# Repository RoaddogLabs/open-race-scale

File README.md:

# open-race-scale
# 
This is the Roaddog Labs fork of Open Race Scale, the open hardware
race car scale from Andrew Jenkins at
https://github.com/jenkinsracing/open-race-scale used under OSHWA and
LGPL 3.0 license.  [Original README.md](orig_README.md)

This fork deals with hardware implementation, hardware packaging and
PCB/PCBA design and fabrication.  This fork uses the software/firmware
from the upstream fork.  Please issue software/firmware pull requests to
the upstream repo.  Pull requests for hardware implementation in this
fork are more than welcome.

The `electrical` dir contains circuit designs and PCB/PCBA info.  It
includes the reference design from the upstream master that uses Chengbo HX711 carriers, a Pi Zero W
based control board with integrated HX711 load cell amps (no carriers) and Pi Hat design using Sparkfun HX711 formfactor carriers.

The `mechanical` dir contains a reference scale pad design and enclosure designs for the various controller boards.

Original designs from Roaddog Labs Ltd are released per the Open Source
Hardware Association guidelines for open source hardware at
http://www.oshwa.org/definition/.

Material specific to the components and documentation that is not
derived from other sources are released under the Creative Commons
Attribution 4.0 International license.

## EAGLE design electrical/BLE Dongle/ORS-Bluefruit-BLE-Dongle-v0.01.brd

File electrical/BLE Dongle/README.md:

# open-race-scale
# 

This is a Bluetooth LE dongle that transmits data from the scale pad to the mobile device.

There is no software or firmware at this time.  This is a reference design using an Adafruit Bluefruit nRF52 module and a Chenbo HX711 module.

This is the Roaddog Labs fork of Open Race Scale, the open hardware
race car scale from Andrew Jenkins at
https://github.com/jenkinsracing/open-race-scale used under OSHWA and
LGPL 3.0 license.  

Original designs from Roaddog Labs Ltd are released per the Open Source
Hardware Association guidelines for open source hardware at
http://www.oshwa.org/definition/.

Material specific to the components and documentation that is not
derived from other sources are released under the Creative Commons
Attribution 4.0 International license.

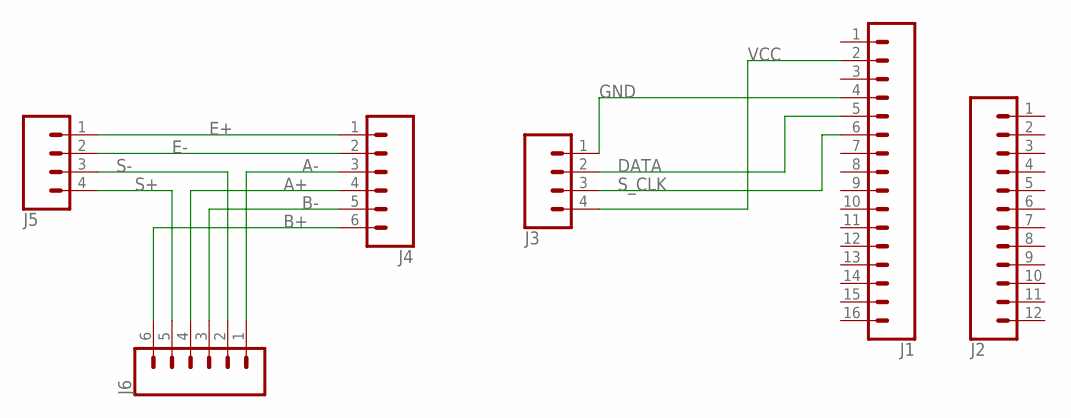
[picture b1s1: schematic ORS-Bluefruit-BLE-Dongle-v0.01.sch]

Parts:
J1: CONN_16; 1X16
J2: CONN_12; 1X12
J3: CONN_04; 1X04
J4, J6: CONN_06SILK_FEMALE_PTH; 1X06
J5: CONN_04SCREW; SCREWTERMINAL-3.5MM-4

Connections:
A+: J4.4, J6.4
A-: J4.3, J6.1
B+: J4.6, J6.6
B-: J4.5, J6.3
DATA: J1.5, J3.2
E+: J4.1, J5.1
E-: J4.2, J5.2
GND: J1.4, J3.1
S+: J5.4, J6.5
S-: J5.3, J6.2
S_CLK: J1.6, J3.3
VCC: J1.2, J3.4

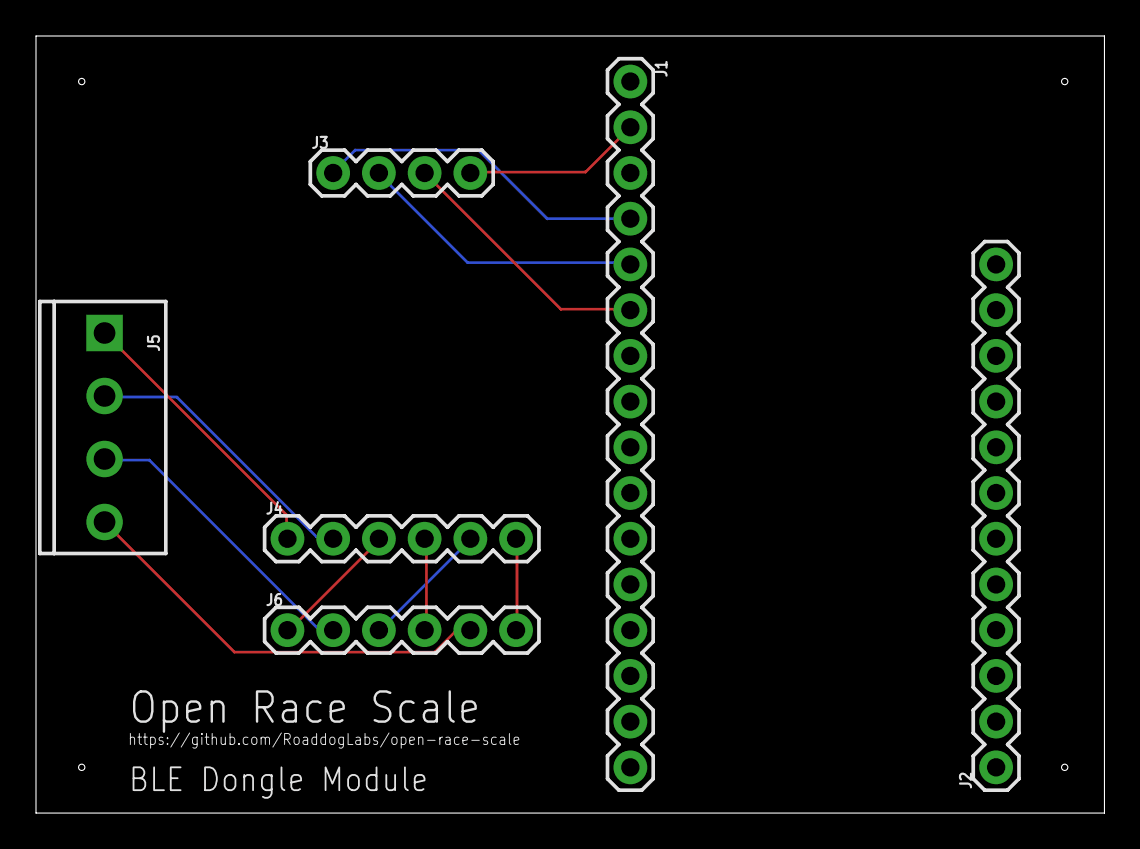
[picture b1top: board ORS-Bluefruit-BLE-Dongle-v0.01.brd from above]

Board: 2 copper layers, 59.4 x 43.2 mm, 6 parts (0 on the bottom side), 12 nets.

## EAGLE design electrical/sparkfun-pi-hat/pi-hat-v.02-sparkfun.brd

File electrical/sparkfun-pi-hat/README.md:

### Open Race Scale Sparkfun HX711 carrier board control board

***THIS BOARD IS NOT YET VALIDATED***

This is an early release version of the control board using Sparkfun HX711 carriers ( https://www.sparkfun.com/products/13879?_ga=2.157347578.176752245.1497484451-1883676811.1497484451 ).  It is not yet ready for production.  It has passed Eagle ERC and DRC for Seeed Fusion PCB.

Forked from https://github.com/jenkinsracing/open-race-scale by Andrew Jenkins license OSHW/public domain, software LGPL 2.0.

Original designs from Roaddog Labs Ltd are released per the Open Source
Hardware Association guidelines for open source hardware at
http://www.oshwa.org/definition/.

Material specific to the components and documentation that is not
derived from other sources are released under the Creative Commons
Attribution 4.0 International license.

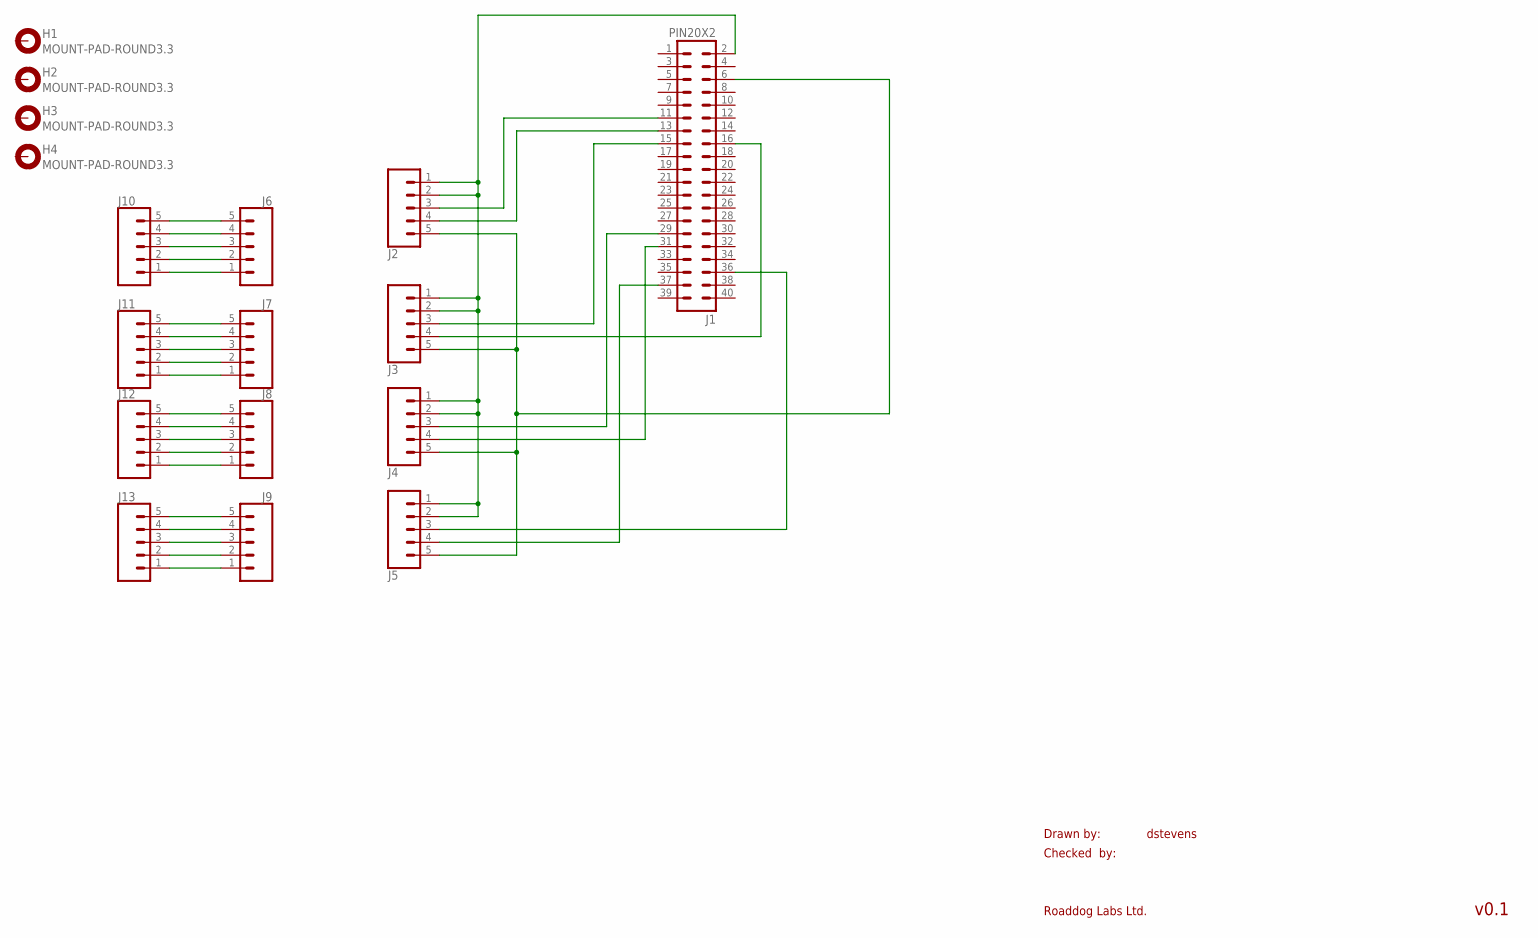
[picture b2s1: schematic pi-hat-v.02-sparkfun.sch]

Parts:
H1, H2, H3, H4: MOUNT-PAD-ROUND3.3; 3,3-PAD
J1: PIN20X2; PIN_20X2
J2, J3, J4, J5, J6, J7, J8, J9, J10, J11, J12, J13: CONN_05; 1X05

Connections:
unnamed: J6.5, J10.5
unnamed: J6.4, J10.4
unnamed: J6.3, J10.3
unnamed: J6.2, J10.2
unnamed: J6.1, J10.1
unnamed: J7.5, J11.5
unnamed: J7.4, J11.4
unnamed: J7.3, J11.3
unnamed: J7.2, J11.2
unnamed: J7.1, J11.1
unnamed: J8.5, J12.5
unnamed: J8.4, J12.4
unnamed: J8.3, J12.3
unnamed: J8.2, J12.2
unnamed: J8.1, J12.1
unnamed: J9.5, J13.5
unnamed: J1.2, J2.1, J2.2, J3.1, J3.2, J4.1, J4.2, J5.1, J5.2
unnamed: J1.6, J2.5, J3.5, J4.5, J5.5
unnamed: J1.11, J2.3
unnamed: J1.13, J2.4
unnamed: J1.15, J3.3
unnamed: J1.16, J3.4
unnamed: J1.37, J5.4
unnamed: J1.36, J5.3
unnamed: J1.31, J4.4
unnamed: J1.29, J4.3
unnamed: J9.4, J13.4
unnamed: J9.3, J13.3
unnamed: J9.2, J13.2
unnamed: J9.1, J13.1

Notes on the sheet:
Drawn by:
Checked by:
Roaddog Labs Ltd.
dstevens
v0.1

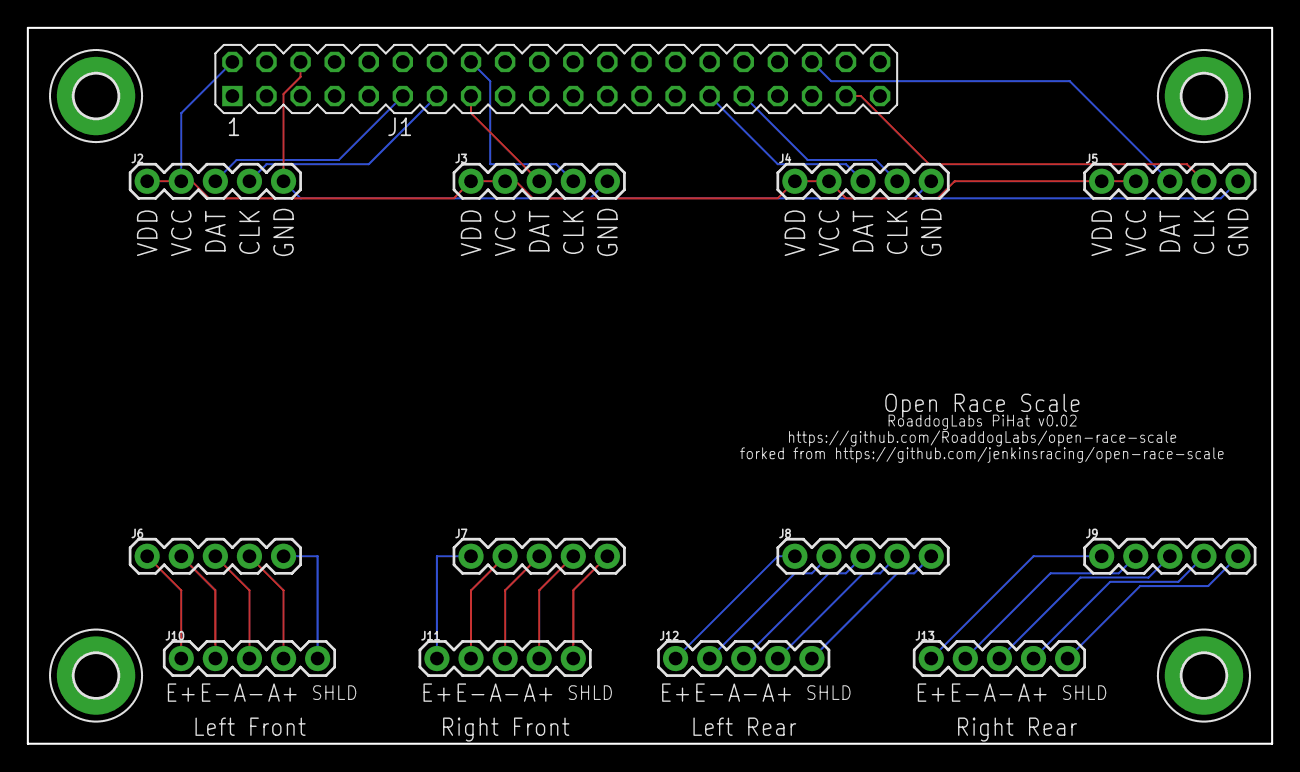
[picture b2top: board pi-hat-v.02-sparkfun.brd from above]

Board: 2 copper layers, 92.7 x 53.3 mm, 17 parts (0 on the bottom side), 30 nets.

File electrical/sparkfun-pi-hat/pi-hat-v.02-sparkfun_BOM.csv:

Designator,Pololu SKU,Qty,
J1,1037,1,https://www.pololu.com/product/1037
"J2,J3,J4,J5,J6,J7,J8,J9",1015,8,https://www.pololu.com/product/1015
"J10,J11,J12,J13",965,1,https://www.pololu.com/product/965

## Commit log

2017-06-26 add schematic and board files for sparkfun pihats
2017-06-26 update schematic and board, generate gerbers
2017-06-27 plate through holes, upload BOM
2017-06-27 update gerbers
2017-07-01 bom for first batch of prototypes
2017-07-10 update readme for pi deployement
2017-07-10 jenkins merge
2017-07-10 update pi-zero board readme
2017-07-10 update spark fun pi-hat readme
2017-07-10 update sparkfun pi-hat readme
2017-07-10 update Chenbo pi-hat BOM
    update Chenbo pi-hat to move Pi and GPIO header to Pololu to
    consolidate vendors
2017-07-13 update Chenbo BOM
2017-07-15 update README
    update main readme to explain differences in fork
2017-07-15 update README
    speling…
2017-07-16 add first rev ble dongle hardware
2017-07-16 update ble readme
2017-07-16 rename ble dir

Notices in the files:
parts and their libraries:
SparkFun-Connectors: Licensing: Creative Commons ShareAlike 4.0 International - https://creativecommons.org/licenses/by-sa/4.0
